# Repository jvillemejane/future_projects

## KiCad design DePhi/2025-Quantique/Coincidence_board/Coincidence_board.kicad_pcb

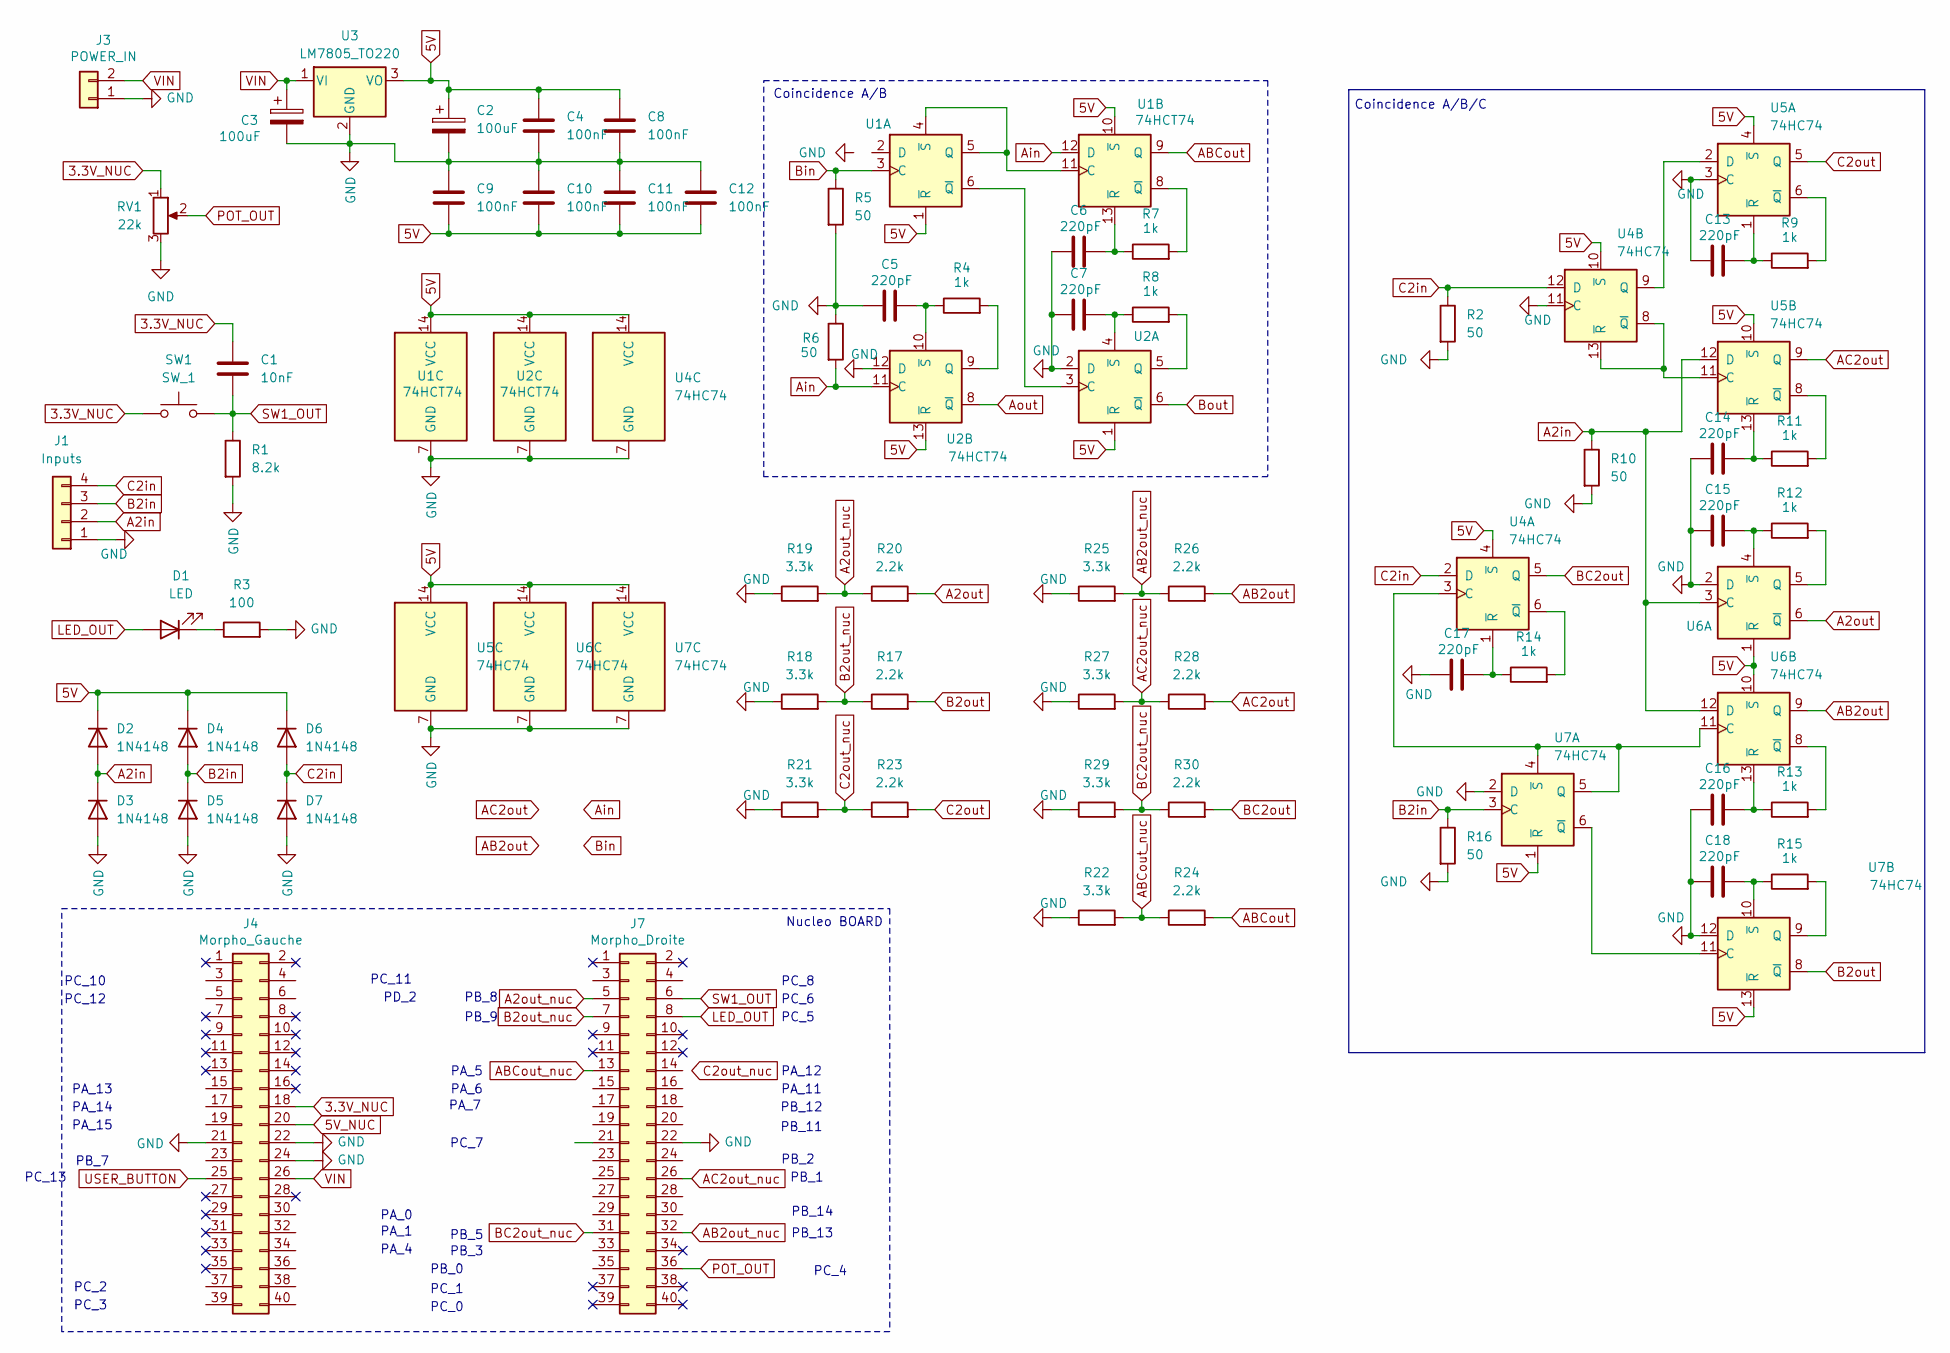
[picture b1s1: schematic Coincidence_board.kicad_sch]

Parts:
C1: 10nF; C_Rect_L7.0mm_W2.5mm_P5.00mm
C2, C3: 100uF; CP_Radial_D6.3mm_P2.50mm
C4, C8, C9, C10, C11, C12: 100nF; C_Rect_L7.0mm_W2.5mm_P5.00mm
C5, C6, C7, C13, C14, C15, C16, C17, C18: 220pF; C_Rect_L4.6mm_W2.0mm_P2.50mm_MKS02_FKP02
D1: LED; LED_D3.0mm_Clear
D2, D3, D4, D5, D6, D7: 1N4148; D_DO-35_SOD27_P7.62mm_Horizontal
J1: Inputs; PinHeader_1x04_P2.54mm_Vertical
J3: POWER_IN; TerminalBlock_Phoenix_MKDS-3-2-5.08_1x02_P5.08mm_Horizontal
J4: Morpho_Gauche; PinHeader_2x20_P2.54mm_Vertical
J7: Morpho_Droite; PinHeader_2x20_P2.54mm_Vertical
R1: 8.2k; R_Axial_DIN0207_L6.3mm_D2.5mm_P10.16mm_Horizontal
R2, R5, R6, R10, R16: 50; R_Axial_DIN0207_L6.3mm_D2.5mm_P10.16mm_Horizontal
R3: 100; R_Axial_DIN0207_L6.3mm_D2.5mm_P10.16mm_Horizontal
R4, R7, R8, R9, R11, R12, R13, R14, R15: 1k; R_Axial_DIN0207_L6.3mm_D2.5mm_P10.16mm_Horizontal
R17, R20, R23, R24, R26, R28, R30: 2.2k; R_Axial_DIN0207_L6.3mm_D2.5mm_P10.16mm_Horizontal
R18, R19, R21, R22, R25, R27, R29: 3.3k; R_Axial_DIN0207_L6.3mm_D2.5mm_P10.16mm_Horizontal
RV1: 22k; Potentiometer_Bourns_3386P_Vertical
SW1: SW_1; Switch
U1, U2: 74HCT74; SO-14_3.9x8.65mm_P1.27mm
U3: LM7805_TO220; TO-220-3_Vertical
U4, U5, U6, U7: 74HC74; SO-14_3.9x8.65mm_P1.27mm

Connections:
3.3V_NUC: C1.1, J4.18, RV1.1, SW1.1
5V: C2.1, C4.1, C8.1, C9.2, C10.2, C11.2, C12.2, D2.1 (K), D4.1 (K), D6.1 (K), U1.1 (~R), U1.10 (~S), U1.14 (VCC), U2.1 (~R), U2.13 (~R), U2.14 (VCC), U3.3 (VO), U4.4 (~S), U4.10 (~S), U4.14 (VCC), U5.4 (~S), U5.10 (~S), U5.14 (VCC), U6.1 (~R), U6.10 (~S), U6.14 (VCC), U7.1 (~R), U7.13 (~R), U7.14 (VCC)
5V_NUC: J4.20
A2in: D2.2 (A), D3.1 (K), J1.2, R10.1, U5.12 (D), U6.3 (C), U6.12 (D)
A2out: R20.2, U6.6 (~Q)
A2out_nuc: J7.5, R19.2, R20.1
AB2out: R26.2, U6.9 (Q)
AB2out_nuc: J7.32, R25.2, R26.1
ABCout: R24.2, U1.9 (Q)
ABCout_nuc: J7.13, R22.2, R24.1
AC2out: R28.2, U5.9 (Q)
AC2out_nuc: J7.26, R27.2, R28.1
Ain: R6.2, U1.12 (D), U2.11 (C)
Aout: U2.8 (~Q)
B2in: D4.2 (A), D5.1 (K), J1.3, R16.1, U7.3 (C)
B2out: R17.2, U7.8 (~Q)
B2out_nuc: J7.7, R17.1, R18.2
BC2out: R30.2, U4.5 (Q)
BC2out_nuc: J7.31, R29.2, R30.1
Bin: R5.1, U1.3 (C)
Bout: U2.6 (~Q)
C2in: D6.2 (A), D7.1 (K), J1.4, R2.1, U4.2 (D), U4.12 (D)
C2out: R23.2, U5.5 (Q)
C2out_nuc: R21.2, R23.1
GND: C2.2, C3.2, C4.2, C5.1, C6.1, C7.1, C8.2, C9.1, C10.1, C11.1, C12.1, C13.1, C14.1, C15.1, C16.1, C17.1, C18.1, D3.2 (A), D5.2 (A), D7.2 (A), J1.1, J3.1, J4.21, J4.22, J4.24, J7.22, R1.2, R2.2, R3.2, R5.2, R6.1, R10.2, R16.2, R18.1, R19.1, R21.1, R22.1, R25.1, R27.1, R29.1, RV1.3, U1.7 (GND), U2.2 (D), U2.7 (GND), U2.12 (D), U3.2 (GND), U4.7 (GND), U4.11 (C), U5.3 (C), U5.7 (GND), U6.2 (D), U6.7 (GND), U7.2 (D), U7.7 (GND), U7.12 (D)
LED_OUT: D1.2 (A), J7.8
unnamed: D1.1 (K), R3.1
unnamed: U1.4 (~S), U1.5 (Q), U1.11 (C)
unnamed: U1.6 (~Q), U2.3 (C)
unnamed: R7.2, U1.8 (~Q)
unnamed: C6.2, R7.1, U1.13 (~R)
unnamed: R8.2, U2.5 (Q)
unnamed: C7.2, R8.1, U2.4 (~S)
unnamed: R4.2, U2.9 (Q)
unnamed: C5.2, R4.1, U2.10 (~S)
unnamed: U4.3 (C), U6.11 (C), U7.4 (~S), U7.5 (Q)
unnamed: R14.2, U4.6 (~Q)
unnamed: C17.2, R14.1, U4.1 (~R)
unnamed: U4.9 (Q), U5.2 (D)
unnamed: U4.8 (~Q), U4.13 (~R), U5.11 (C)
unnamed: R9.2, U5.6 (~Q)
unnamed: C13.2, R9.1, U5.1 (~R)
unnamed: R11.2, U5.8 (~Q)
unnamed: C14.2, R11.1, U5.13 (~R)
unnamed: R12.2, U6.5 (Q)
unnamed: C15.2, R12.1, U6.4 (~S)
unnamed: R13.2, U6.8 (~Q)
unnamed: C16.2, R13.1, U6.13 (~R)
unnamed: U7.6 (~Q), U7.11 (C)
unnamed: R15.2, U7.9 (Q)
unnamed: C18.2, R15.1, U7.10 (~S)
POT_OUT: J7.36, RV1.2
SW1_OUT: C1.2, J7.6, R1.1, SW1.2
USER_BUTTON: J4.25
VIN: C3.1, J3.2, J4.26, U3.1 (VI)

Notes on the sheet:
PA_12
PC_2
PB_8
PA_7
PB_0
PC_8
PC_11
PB_3
PA_5
PB_13
PA_14
Coincidence A/B
PB_11
Coincidence A/B/C
PC_7
PB_9
PC_5
PB_2
PC_1
PC_12
PB_14
PC_13
PD_2
PA_15
PC_10
PA_11
PC_4
PA_6
PA_13
PB_7
PA_1
Nucleo BOARD
PC_0
PB_12
PC_3
PB_1
PA_0
PA_4
PC_6
PB_5

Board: 2 copper layers, 69 parts (0 on the bottom side), 51 nets, no tracks yet.

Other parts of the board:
M: MountingHole_3.2mm_M3

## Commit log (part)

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2024-03-17 Update Future Projects
2024-03-17 Update C++ image processing
2024-03-17 Update Opening and Closing transform
2024-03-17 Update C++ and Python
2024-03-17 Update OpenCV on C++ test
2024-03-19 Update Demo Image Processing
2024-03-19 Update Demo Images processing
2024-03-19 Update Image Processing Demo
    Basic filters are ok / Open an image file and adapt display
2024-03-19 Update Demo
2024-03-21 Adding Machine Learning Labworks
2024-03-22 Update Image Processing
2024-03-22 update Demo
    Need to change main design !!
2024-03-22 Update Image Process
2024-03-23 Binarization complete on Image Processing Demo
    To do : update other processes (blur...)
2024-03-23 update Image Processing / Adding kernel_widget file and class
2024-03-23 Update Demo Image Processing
    Still problems with kernel modification
2024-03-23 Update Image Processing tests
2024-03-24 Update Images for image processing
2024-03-24 Move image processing
2024-04-23 Update Dephi Harpe 2024
2024-04-24 Update Dephi 2024 - Harpe
2024-05-05 Add Illumination lights project in future demo
2024-08-19 Nothing !
2024-09-08 Update control and signal python libs and examples
2024-11-06 Update Quantum Board CoincABC
2024-11-06 Remove Dephi Quantum 2025
2024-11-14 Move old lensepy
2025-03-24 Kivy Test for Gui development in Python
2025-03-31 Suppression et reorganisation
2025-08-20 Add Sissi graphics flexion 3 points
